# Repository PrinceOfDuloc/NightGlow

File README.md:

**NightGlow** is a smart hallway night light designed from the ground up with a focus on efficiency, reliability, and engineering transparency. Rather than treating it as a simple LED lamp, the project explores every major subsystem—from optical design and power electronics to analog sensing and firmware architecture.

The hardware combines a high-efficiency constant-current LED driver, a mmWave motion sensor, a photodiode-based ambient light measurement circuit, and a custom control board built around an AVR microcontroller. The firmware implements adaptive brightness control, configurable operating modes, automatic standby behaviour, and non-blocking task scheduling while keeping resource usage minimal.

This repository documents the complete engineering process, including design decisions, calculations, simulations, component selection, bench measurements, firmware implementation, PCB design, and validation. The report explains not only **what** was built, but also **why** each engineering decision was made and what alternatives were considered.

📖 **Start here:** [**Design Walkthrough**](https://princeofduloc.github.io/NightGlow/Design%20Walkthrough/NightGlow%20Design%20Walkthrough.html)

Whether you're interested in embedded firmware, analog circuit design, power electronics, PCB development, or simply enjoy seeing how a product is engineered from first principles, the design report is intended to provide a complete and reproducible walkthrough of the project.

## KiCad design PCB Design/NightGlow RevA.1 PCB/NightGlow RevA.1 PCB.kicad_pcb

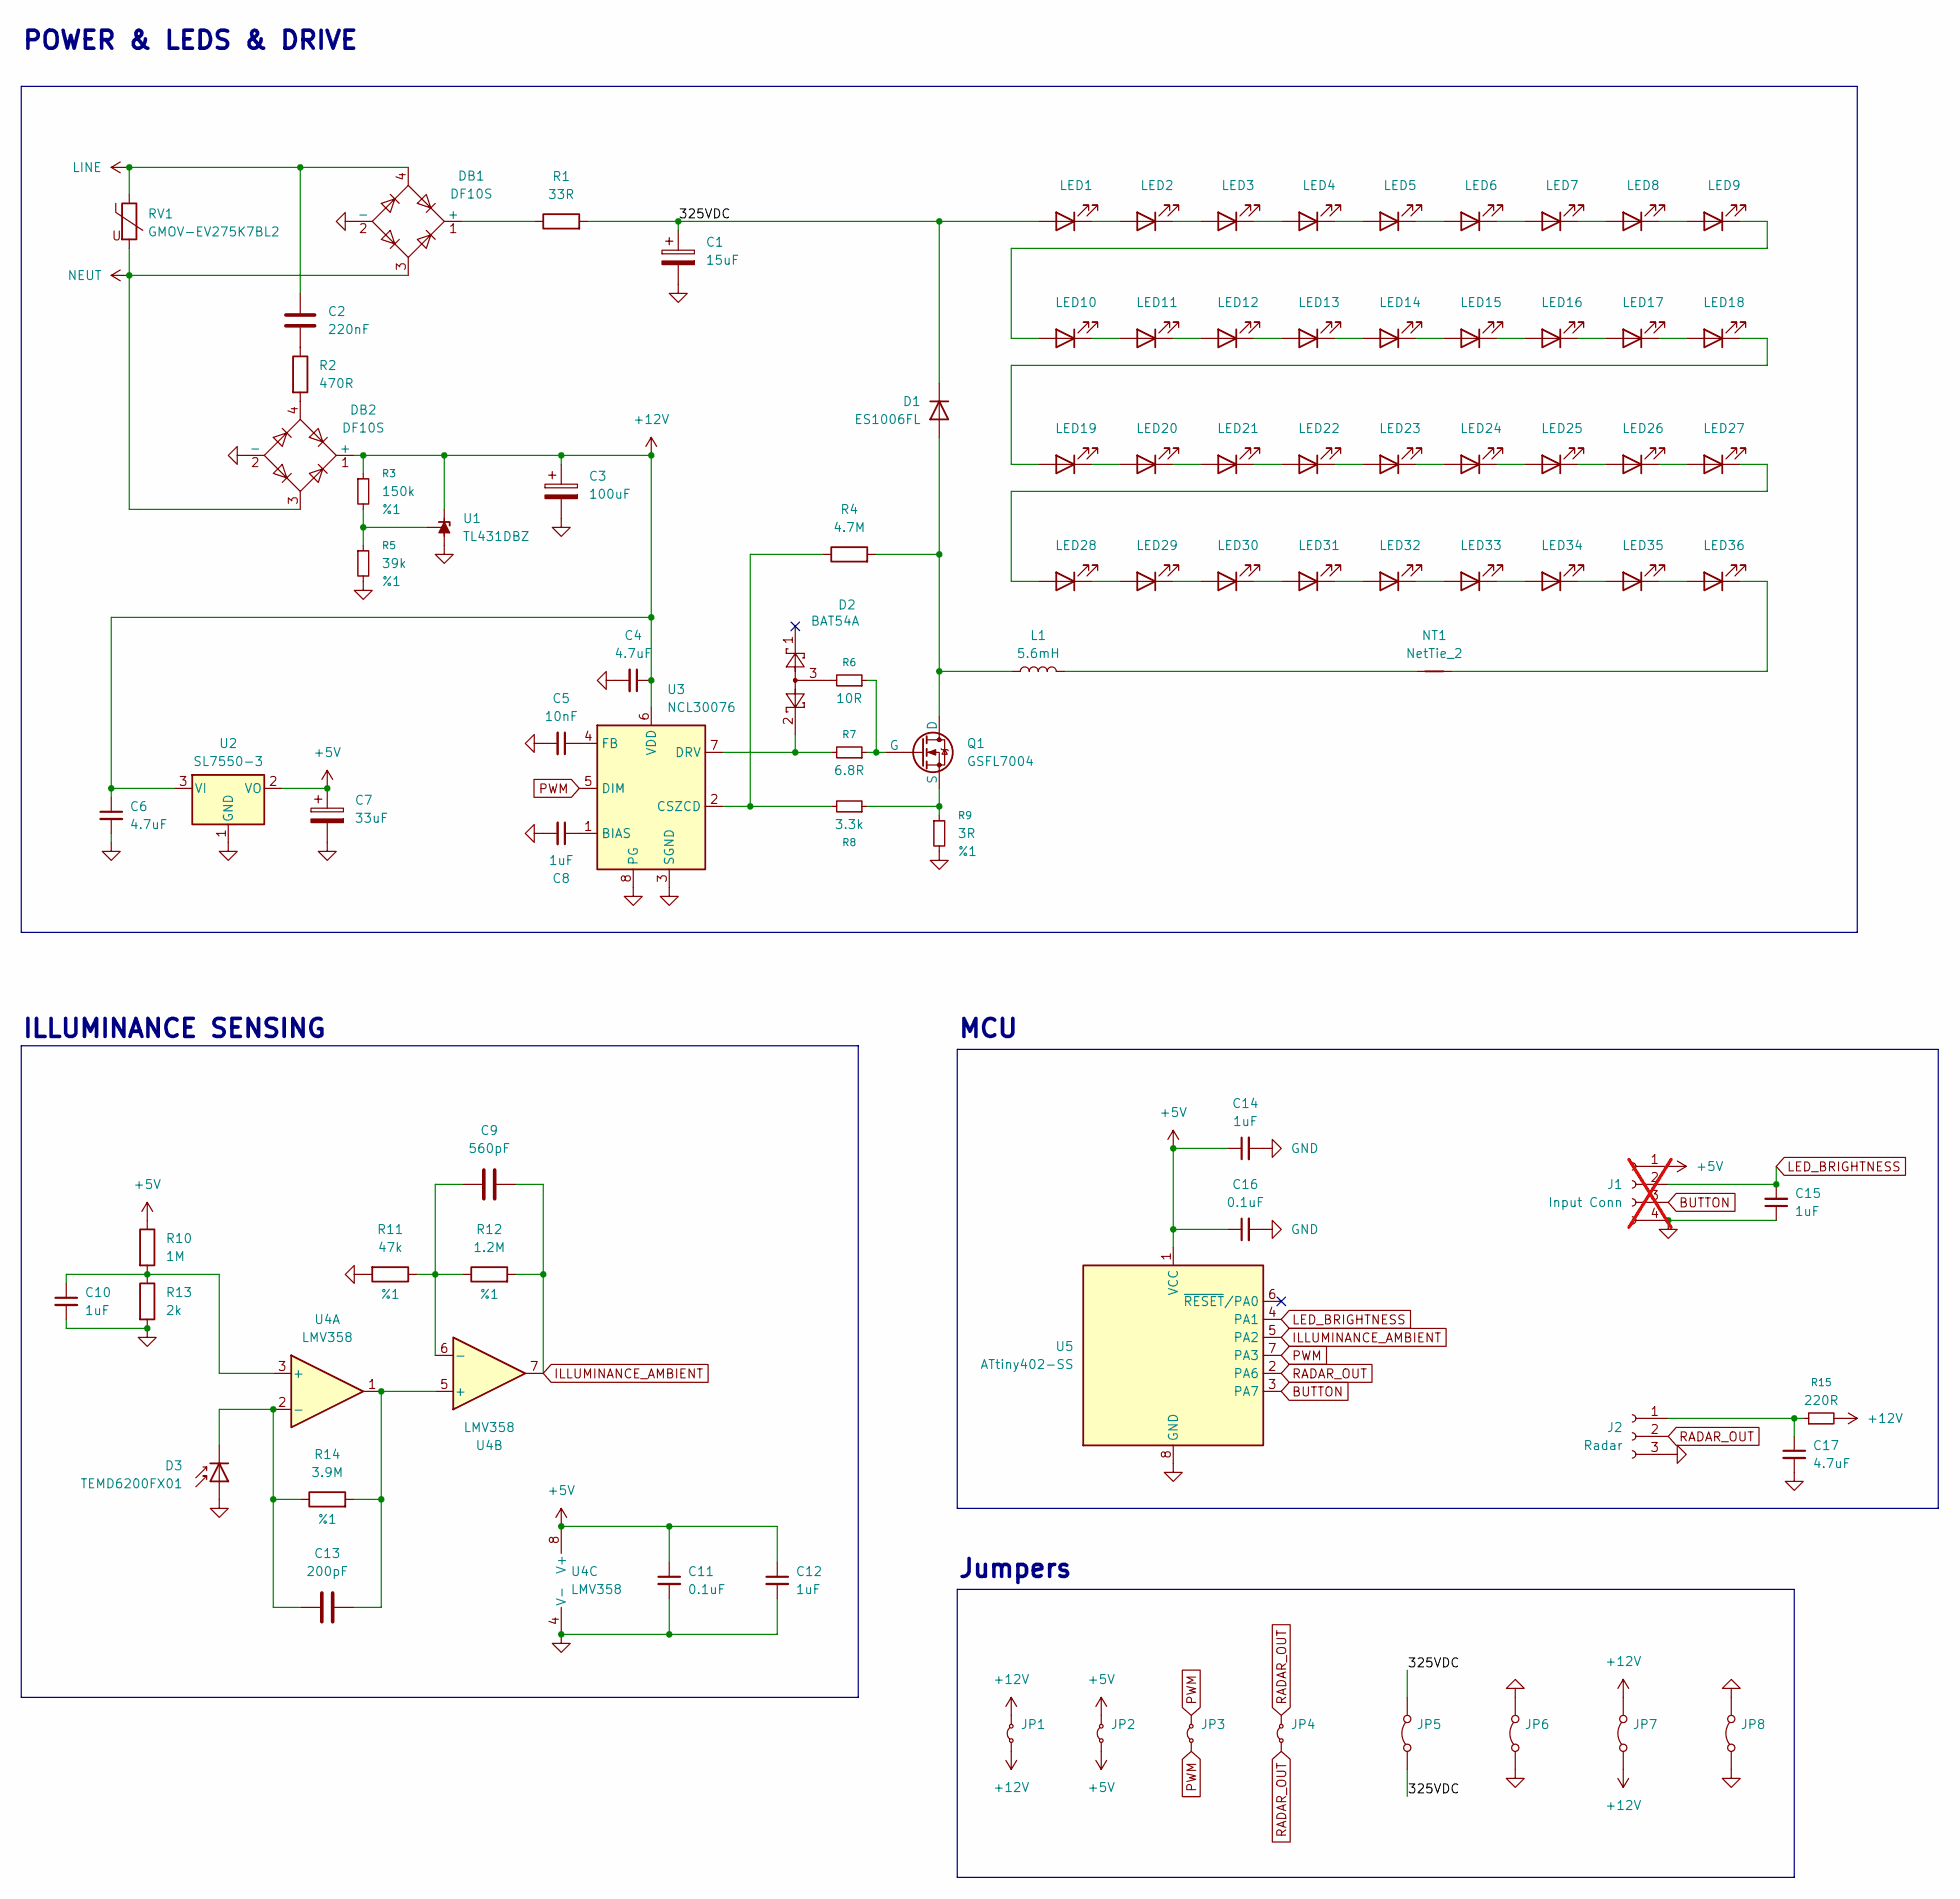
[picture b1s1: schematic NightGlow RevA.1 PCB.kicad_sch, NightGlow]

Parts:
C1: 15uF; CP_Radial_D10.0mm_P5.0mm_H22.0mm_Horizontal
C2: 220nF; C_Rect_L13.0mm_W8.0mm_P10.00mm_FKS3_FKP3_MKS4
C3: 100uF; CP_Elec_6.3x7.7
C4, C6, C17: 4.7uF; C_0805_2012Metric
C5: 10nF; C_0603_1608Metric
C7: 33uF; CP_Elec_5x5.4
C8, C10, C12, C14, C15: 1uF; C_0603_1608Metric
C9: 560pF; C_0603_1608Metric
C11, C16: 0.1uF; C_0603_1608Metric
C13: 200pF; C_0603_1608Metric
D1: ES1006FL; SOD-123FL_SME
D2: BAT54A; SOT-23
D3: TEMD6200FX01; LED_0805_2012Metric
DB1, DB2: DF10S; Diode_Bridge_OnSemi_SDIP-4L
J1: Input Conn; PinHeader_1x04_P2.54mm_Vertical; not fitted
J2: Radar; PinHeader_1x03_P2.54mm_Vertical
JP1, JP2, JP3, JP4: R_Axial_DIN0204_L3.6mm_D1.6mm_P7.62mm_Horizontal
JP5: R_Axial_DIN0309_L9.0mm_D3.2mm_P20.32mm_Horizontal
JP6, JP7, JP8: R_Axial_DIN0207_L6.3mm_D2.5mm_P15.24mm_Horizontal
L1: 5.6mH; L_Bourns_SRR1208_12.7x12.7mm
LED1, LED2, LED3, LED4, LED5, LED6, LED7, LED8, LED9, LED10, LED11, LED12, LED13, LED14, LED15, LED16, LED17, LED18, LED19, LED20, LED21, LED22, LED23, LED24, LED25, LED26, LED27, LED28, LED29, LED30, LED31, LED32, LED33, LED34, LED35, LED36: LED; LED_PLCC_2835
NT1: NetTie_2; NetTie-2_SMD_Pad2.0mm
Q1: GSFL7004; SOT-223-3
R1: 33R; R_1206_3216Metric
R2: 470R; R_1206_3216Metric
R3: 150k; R_0603_1608Metric
R4: 4.7M; R_2010_5025Metric
R5: 39k; R_0603_1608Metric
R6: 10R; R_0603_1608Metric
R7: 6.8R; R_0603_1608Metric
R8: 3.3k; R_0603_1608Metric
R9: 3R; R_0603_1608Metric
R10: 1M; R_0603_1608Metric
R11: 47k; R_0603_1608Metric
R12: 1.2M; R_0603_1608Metric
R13: 2k; R_0603_1608Metric
R14: 3.9M; R_0603_1608Metric
R15: 220R; R_0603_1608Metric
RV1: GMOV-EV275K7BL2
U1: TL431DBZ; SOT-23
U2: SL7550-3; SOT-23
U3: NCL30076; SOIC-8_3.9x4.9mm_P1.27mm
U4: LMV358; SSOP-8_3.9x5.05mm_P1.27mm
U5: ATtiny402-SS; SOIC-8_3.9x4.9mm_P1.27mm

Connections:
+5V: C7.1, C11.1, C12.1, C14.1, C16.1, J1.1, JP2.1 (A), JP2.2 (B), R10.1, U2.2 (VO), U4.8 (V+), U5.1 (VCC)
+12V: C3.1, C4.1, C6.1, DB2.1 (+), JP1.1 (A), JP1.2 (B), JP7.1 (A), JP7.2 (B), R3.1, R15.2, U1.1 (K), U2.3 (VI), U3.6 (VDD)
/325VDC: C1.1, D1.1 (K), JP5.1 (A), JP5.2 (B), LED1.2 (A), R1.2
BUTTON: J1.3, U5.3 (PA7)
GND: C1.2, C3.2, C4.2, C5.2, C6.2, C7.2, C8.2, C10.2, C11.2, C12.2, C14.2, C15.1, C16.2, C17.2, D3.2 (A), DB1.2 (-), DB2.2 (-), J1.4, J2.3, JP6.1 (A), JP6.2 (B), JP8.1 (A), JP8.2 (B), R5.2, R9.2, R11.2, R13.2, U1.3 (A), U2.1 (GND), U3.3 (SGND), U3.8 (PG), U4.4 (V-), U5.8 (GND)
ILLUMINANCE_AMBIENT: C9.2, R12.2, U4.7, U5.5 (PA2)
LED_BRIGHTNESS: C15.2, J1.2, U5.4 (PA1)
LINE: C2.1, DB1.4, RV1.1
NEUT: DB1.3, DB2.3, RV1.2
unnamed: C2.2, R2.1
unnamed: D1.2 (A), L1.1, Q1.1 (D), R4.2
unnamed: D2.3, R6.2
unnamed: C13.1, D3.1 (K), R14.1, U4.2 (-)
unnamed: DB1.1 (+), R1.1
unnamed: DB2.4, R2.2
unnamed: C17.1, J2.1, R15.1
unnamed: L1.2, NT1.1
unnamed: LED1.1 (K), LED2.2 (A)
unnamed: LED2.1 (K), LED3.2 (A)
unnamed: LED3.1 (K), LED4.2 (A)
unnamed: LED4.1 (K), LED5.2 (A)
unnamed: LED5.1 (K), LED6.2 (A)
unnamed: LED6.1 (K), LED7.2 (A)
unnamed: LED7.1 (K), LED8.2 (A)
unnamed: LED8.1 (K), LED9.2 (A)
unnamed: LED9.1 (K), LED10.2 (A)
unnamed: LED10.1 (K), LED11.2 (A)
unnamed: LED11.1 (K), LED12.2 (A)
unnamed: LED12.1 (K), LED13.2 (A)
unnamed: LED13.1 (K), LED14.2 (A)
unnamed: LED14.1 (K), LED15.2 (A)
unnamed: LED15.1 (K), LED16.2 (A)
unnamed: LED16.1 (K), LED17.2 (A)
unnamed: LED17.1 (K), LED18.2 (A)
unnamed: LED18.1 (K), LED19.2 (A)
unnamed: LED19.1 (K), LED20.2 (A)
unnamed: LED20.1 (K), LED21.2 (A)
unnamed: LED21.1 (K), LED22.2 (A)
unnamed: LED22.1 (K), LED23.2 (A)
unnamed: LED23.1 (K), LED24.2 (A)
unnamed: LED24.1 (K), LED25.2 (A)
unnamed: LED25.1 (K), LED26.2 (A)
unnamed: LED26.1 (K), LED27.2 (A)
unnamed: LED27.1 (K), LED28.2 (A)
unnamed: LED28.1 (K), LED29.2 (A)
unnamed: LED29.1 (K), LED30.2 (A)
unnamed: LED30.1 (K), LED31.2 (A)
unnamed: LED31.1 (K), LED32.2 (A)
unnamed: LED32.1 (K), LED33.2 (A)
unnamed: LED33.1 (K), LED34.2 (A)
unnamed: LED34.1 (K), LED35.2 (A)
unnamed: LED35.1 (K), LED36.2 (A)
unnamed: LED36.1 (K), NT1.2
unnamed: Q1.2 (G), R6.1, R7.1
unnamed: Q1.3 (S), R8.1, R9.1
unnamed: R3.2, R5.1, U1.2 (REF)
unnamed: C8.1, U3.1 (BIAS)
unnamed: R4.1, R8.2, U3.2 (CSZCD)
unnamed: D2.2, R7.2, U3.7 (DRV)
unnamed: C5.1, U3.4 (FB)
unnamed: C10.1, R10.2, R13.1, U4.3 (+)
unnamed: C13.2, R14.2, U4.1, U4.5 (+)
unnamed: C9.1, R11.1, R12.1, U4.6 (-)
PWM: JP3.1 (A), JP3.2 (B), U3.5 (DIM), U5.7 (PA3)
RADAR_OUT: J2.2, JP4.1 (A), JP4.2 (B), U5.2 (PA6)

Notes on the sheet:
MCU
Jumpers
ILLUMINANCE SENSING
POWER & LEDS & DRIVE

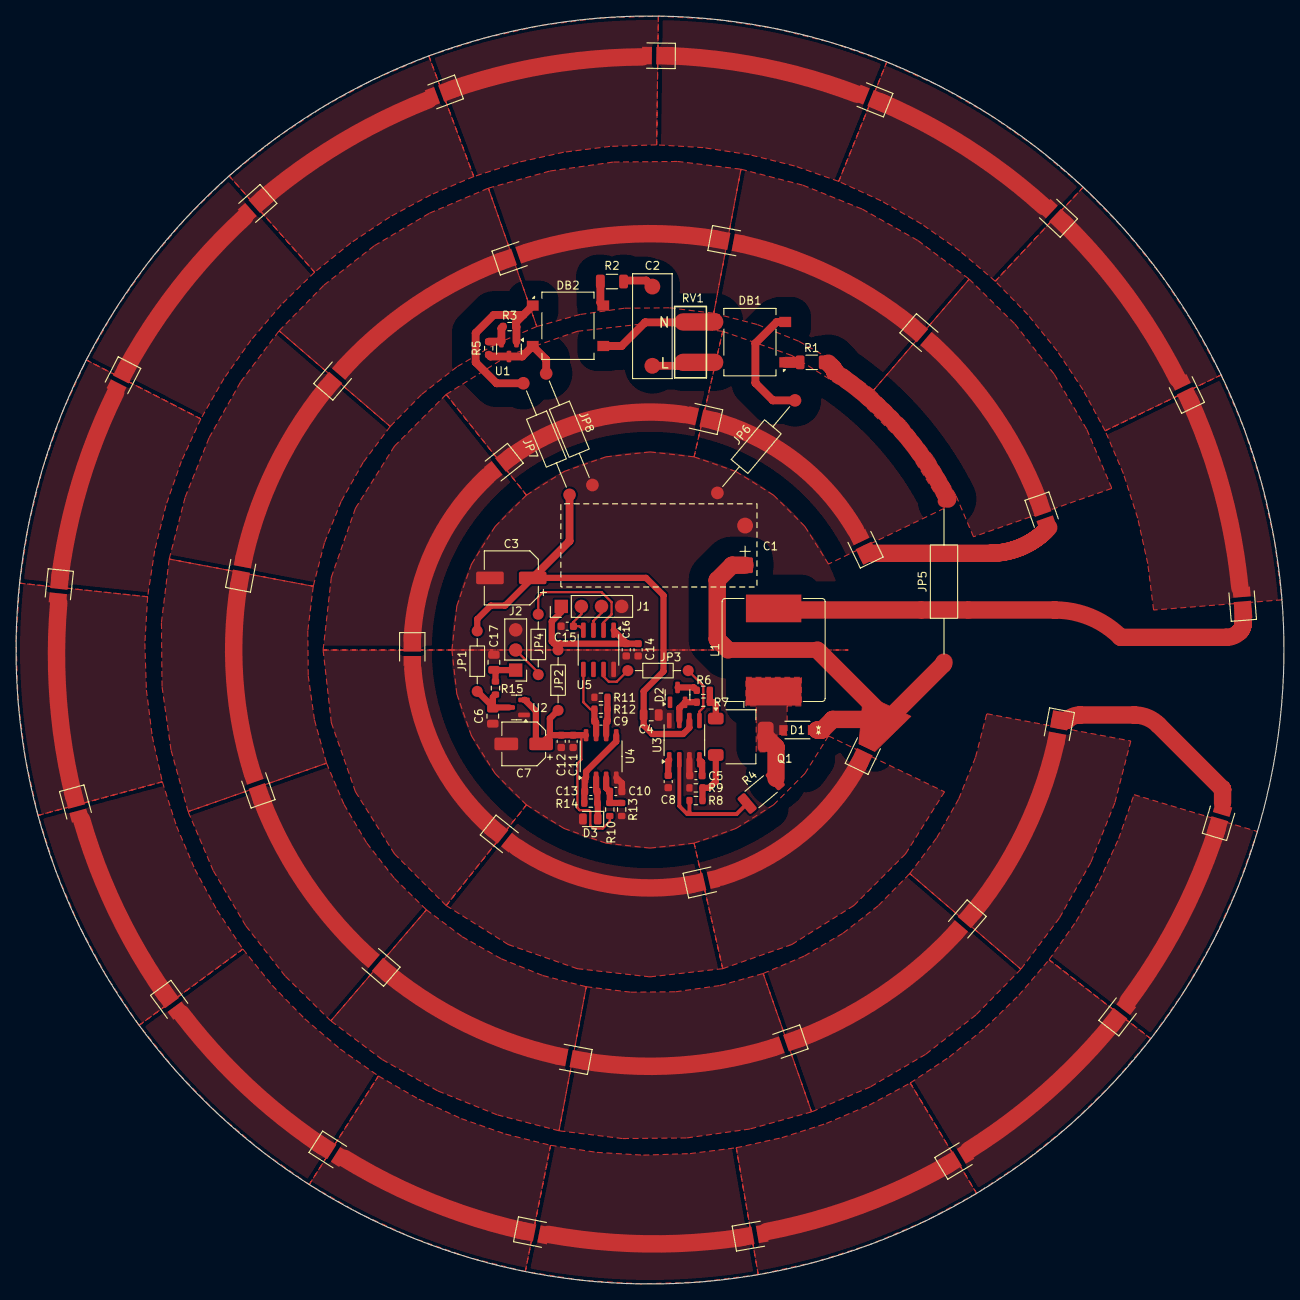
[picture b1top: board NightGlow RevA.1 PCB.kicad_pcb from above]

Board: 2 copper layers, 160.0 x 160.0 mm, 92 parts (0 on the bottom side), 65 nets.

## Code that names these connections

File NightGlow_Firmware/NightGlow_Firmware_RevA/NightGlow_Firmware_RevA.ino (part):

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*/
#include <EEPROM.h>

#define RADAR_OUT_PIN 6  // PA6 (physical 2)
#define BUTTON_PIN 7     // PA7 (physical 3)
#define PWM_PIN 3        // PA3 (physical 7)

const uint32_t ticksWithoutMotion_LIM_Options[] = { 600, 2400, 18000, 3456000, UINT32_MAX };  // 30 seconds, 2 minutes, 15 minutes, 48 hours, ~7 years

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uint8_t luxSamples_remaining = 0;

void setup() {
  PORTA.DIR |= (1 << PWM_PIN);                              // Define PWM pin as Output, only PA1, PA2 or PA3 are hardware PWM pins for TCA0
  PORTA.PIN6CTRL = PORT_ISC_RISING_gc;                      // Radar DO interrupt
  PORTA.PIN7CTRL = PORT_PULLUPEN_bm | PORT_ISC_FALLING_gc;  // BUTTON inputpullup and Interrupt enabled

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  TCA0.SPLIT.CTRLA = 0;                                                           // (Required by the Core)disable TCA0 and set divider to 1
  TCA0.SPLIT.CTRLESET = TCA_SPLIT_CMD_RESET_gc | 0x03;                            // (Required by the Core) set CMD to RESET to do a hard reset of TCA0.
  TCA0.SINGLE.CTRLB = (TCA_SINGLE_CMP0EN_bm | TCA_SINGLE_WGMODE_SINGLESLOPE_gc);  // PWM on WO0, single slope PWM mode
  PORTMUX.CTRLC = PORTMUX_TCA00_DEFAULT_gc;                                       // Routes TCA0 WO0 -> PA3 (WO0 normally defaults to PA3 but megaTinyCore modifies it at startup making it is necessary to restore to default)
  TCA0.SINGLE.PER = UINT8_MAX;                                                    // Count up to 255 for each period
  TCA0.SINGLE.CTRLA = TCA_SINGLE_CLKSEL_DIV4_gc;                                  // Set Prescaler to 4 -> F_PWM = F_CPU / Prescaler -> F_PWM = 2MHz/(4 * (255+1)) = 1953Hz

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
void loop() {
  if (checkButtonFlag_Clear()) Settings();
  if (inputRead(RADAR_OUT_PIN)) ticksWithoutMotion = 0;

  if (ticksWithoutMotion < ticksWithoutMotion_LIM_Options[ticksWithoutMotion_LIM]) {  // If the area is occupied...
    if (luxCheckEN) {
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  __asm__ __volatile__("sleep");    // Trigger sleep using inline assembly
}

uint16_t ADCRead(uint8_t pin) {  // 1: PA1, 2: PA2
  if (pin == 1) ADC0.MUXPOS = ADC_MUXPOS_AIN1_gc;
  else if (pin == 2) ADC0.MUXPOS = ADC_MUXPOS_AIN2_gc;
  ADC0.COMMAND = ADC_STCONV_bm;  // Start the conversion
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
ISR(PORTA_PORT_vect) {
  if (PORTA.INTFLAGS & (1 << BUTTON_PIN)) ButtonFlag = true;  // post usable flag
  PORTA.INTFLAGS = (1 << RADAR_OUT_PIN) | (1 << BUTTON_PIN);  // clear flags
}

void Settings() {
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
